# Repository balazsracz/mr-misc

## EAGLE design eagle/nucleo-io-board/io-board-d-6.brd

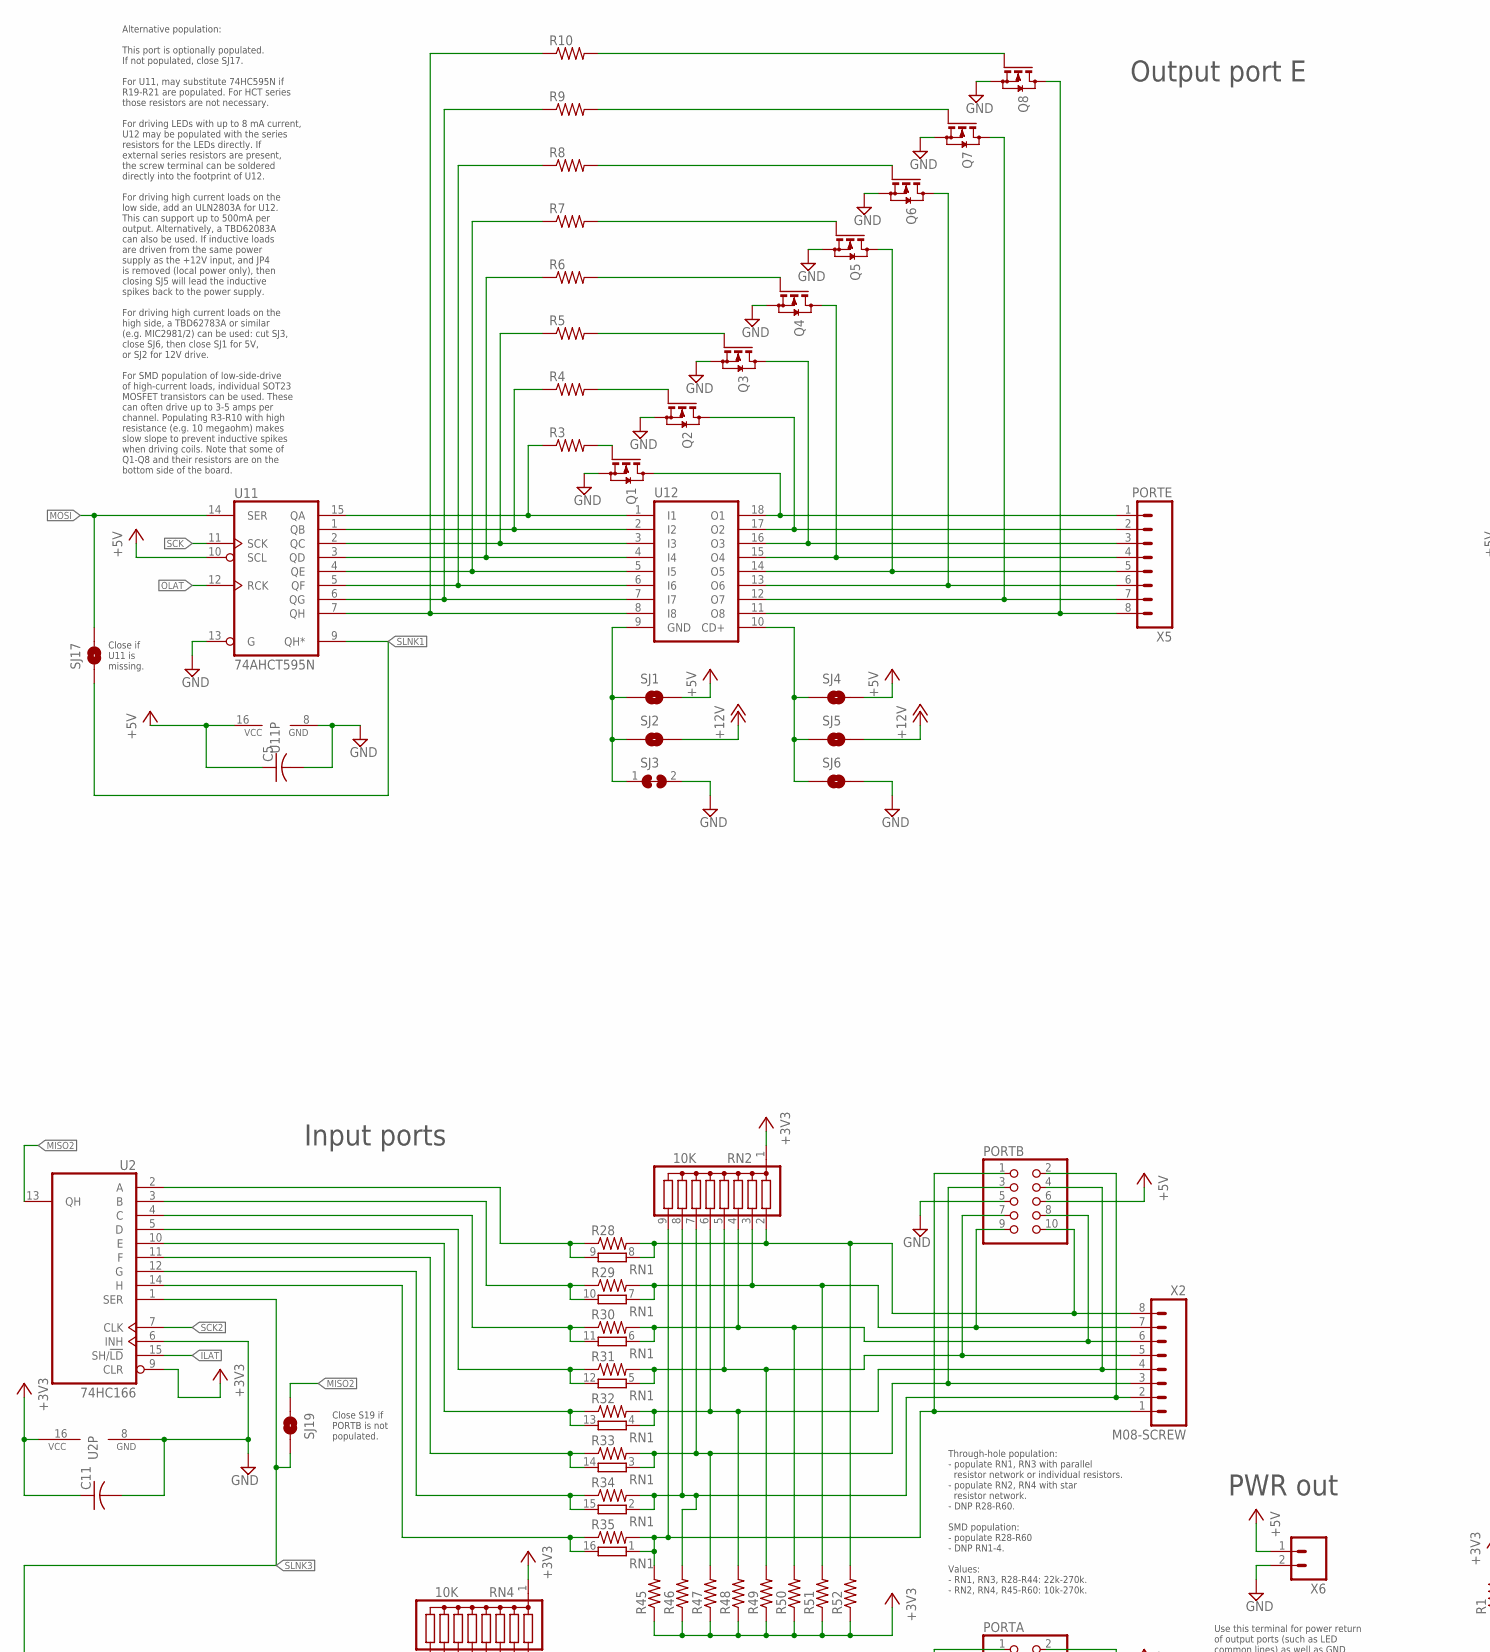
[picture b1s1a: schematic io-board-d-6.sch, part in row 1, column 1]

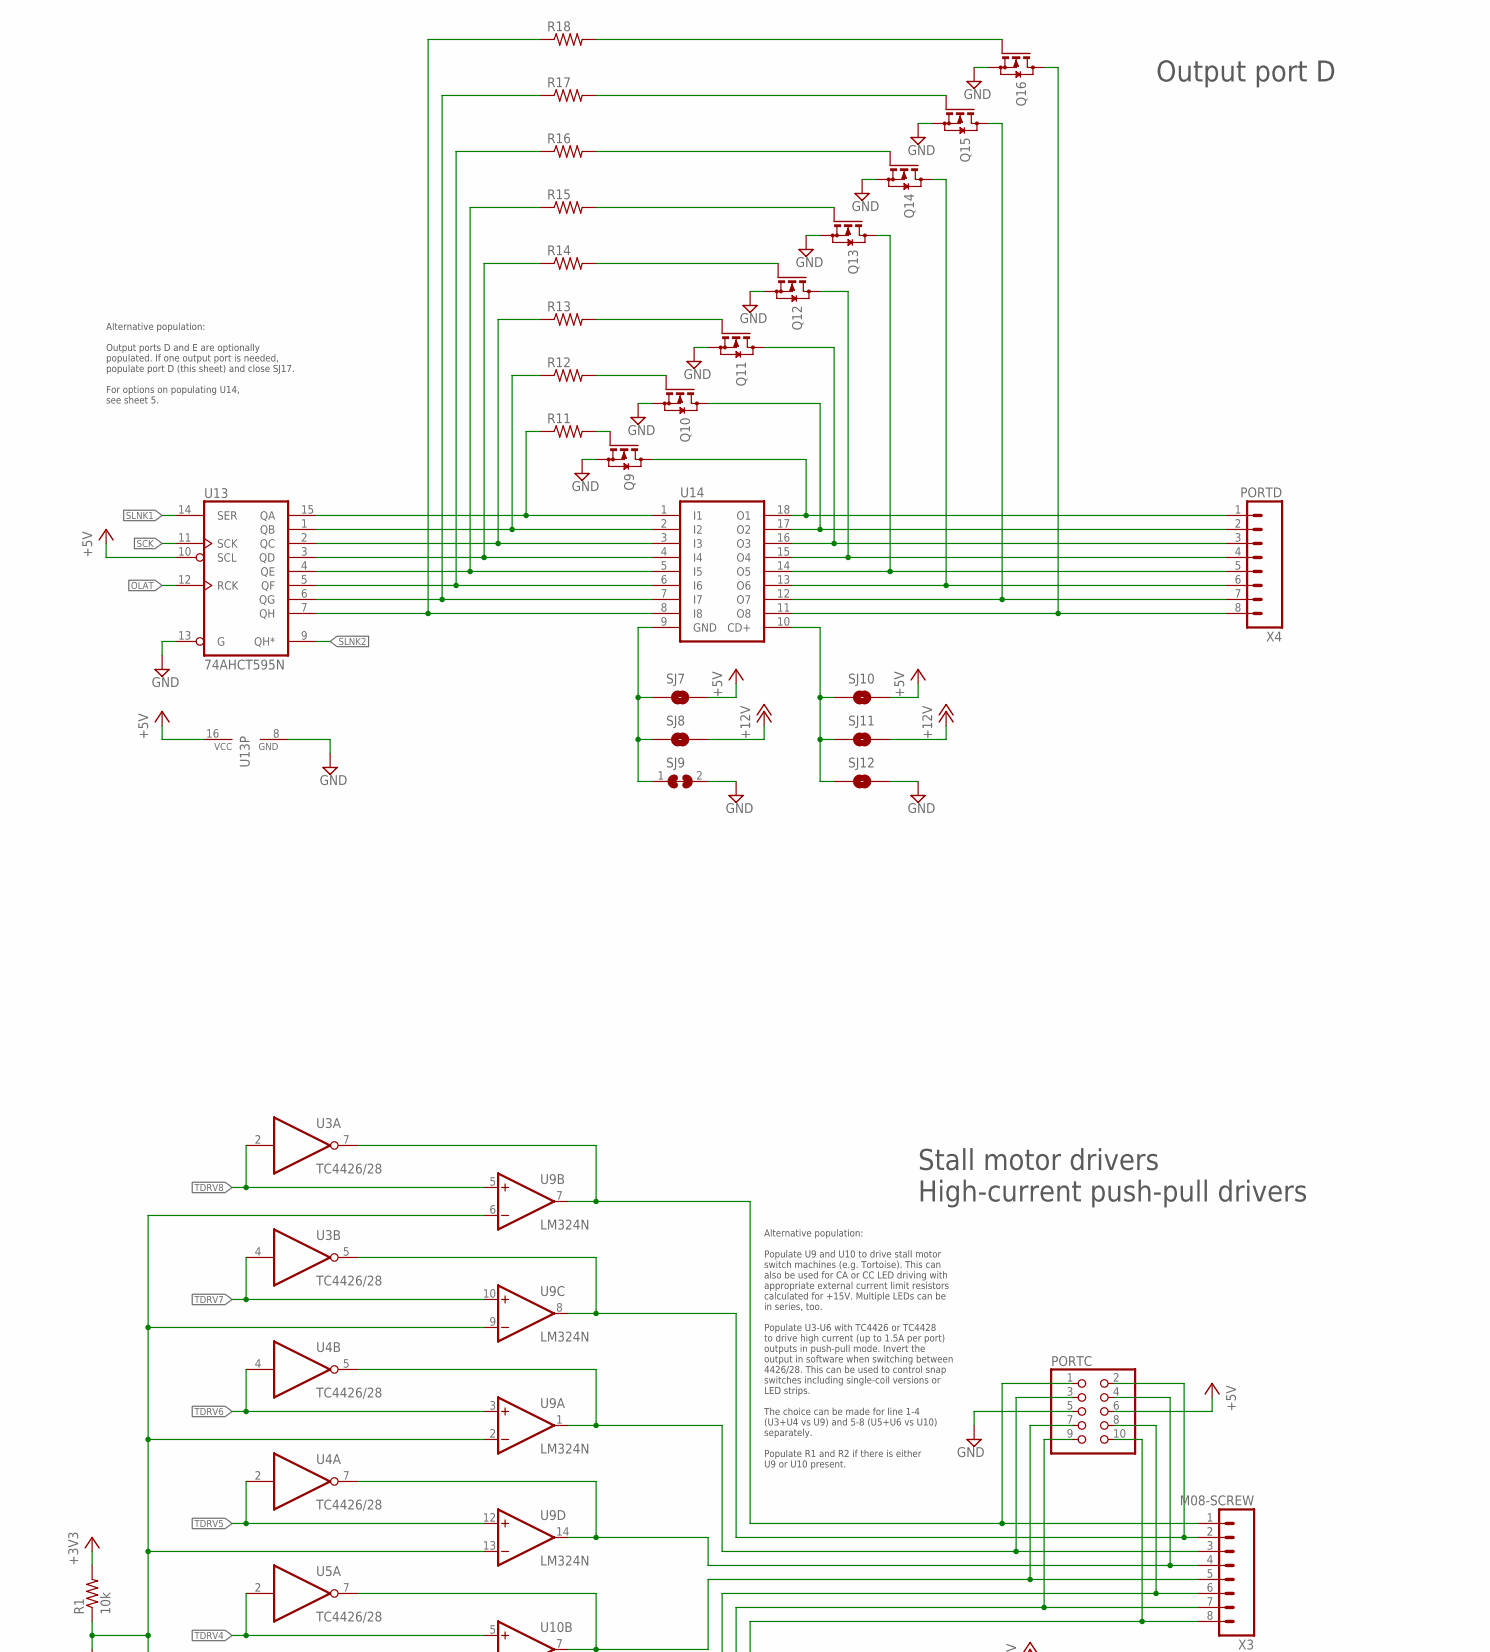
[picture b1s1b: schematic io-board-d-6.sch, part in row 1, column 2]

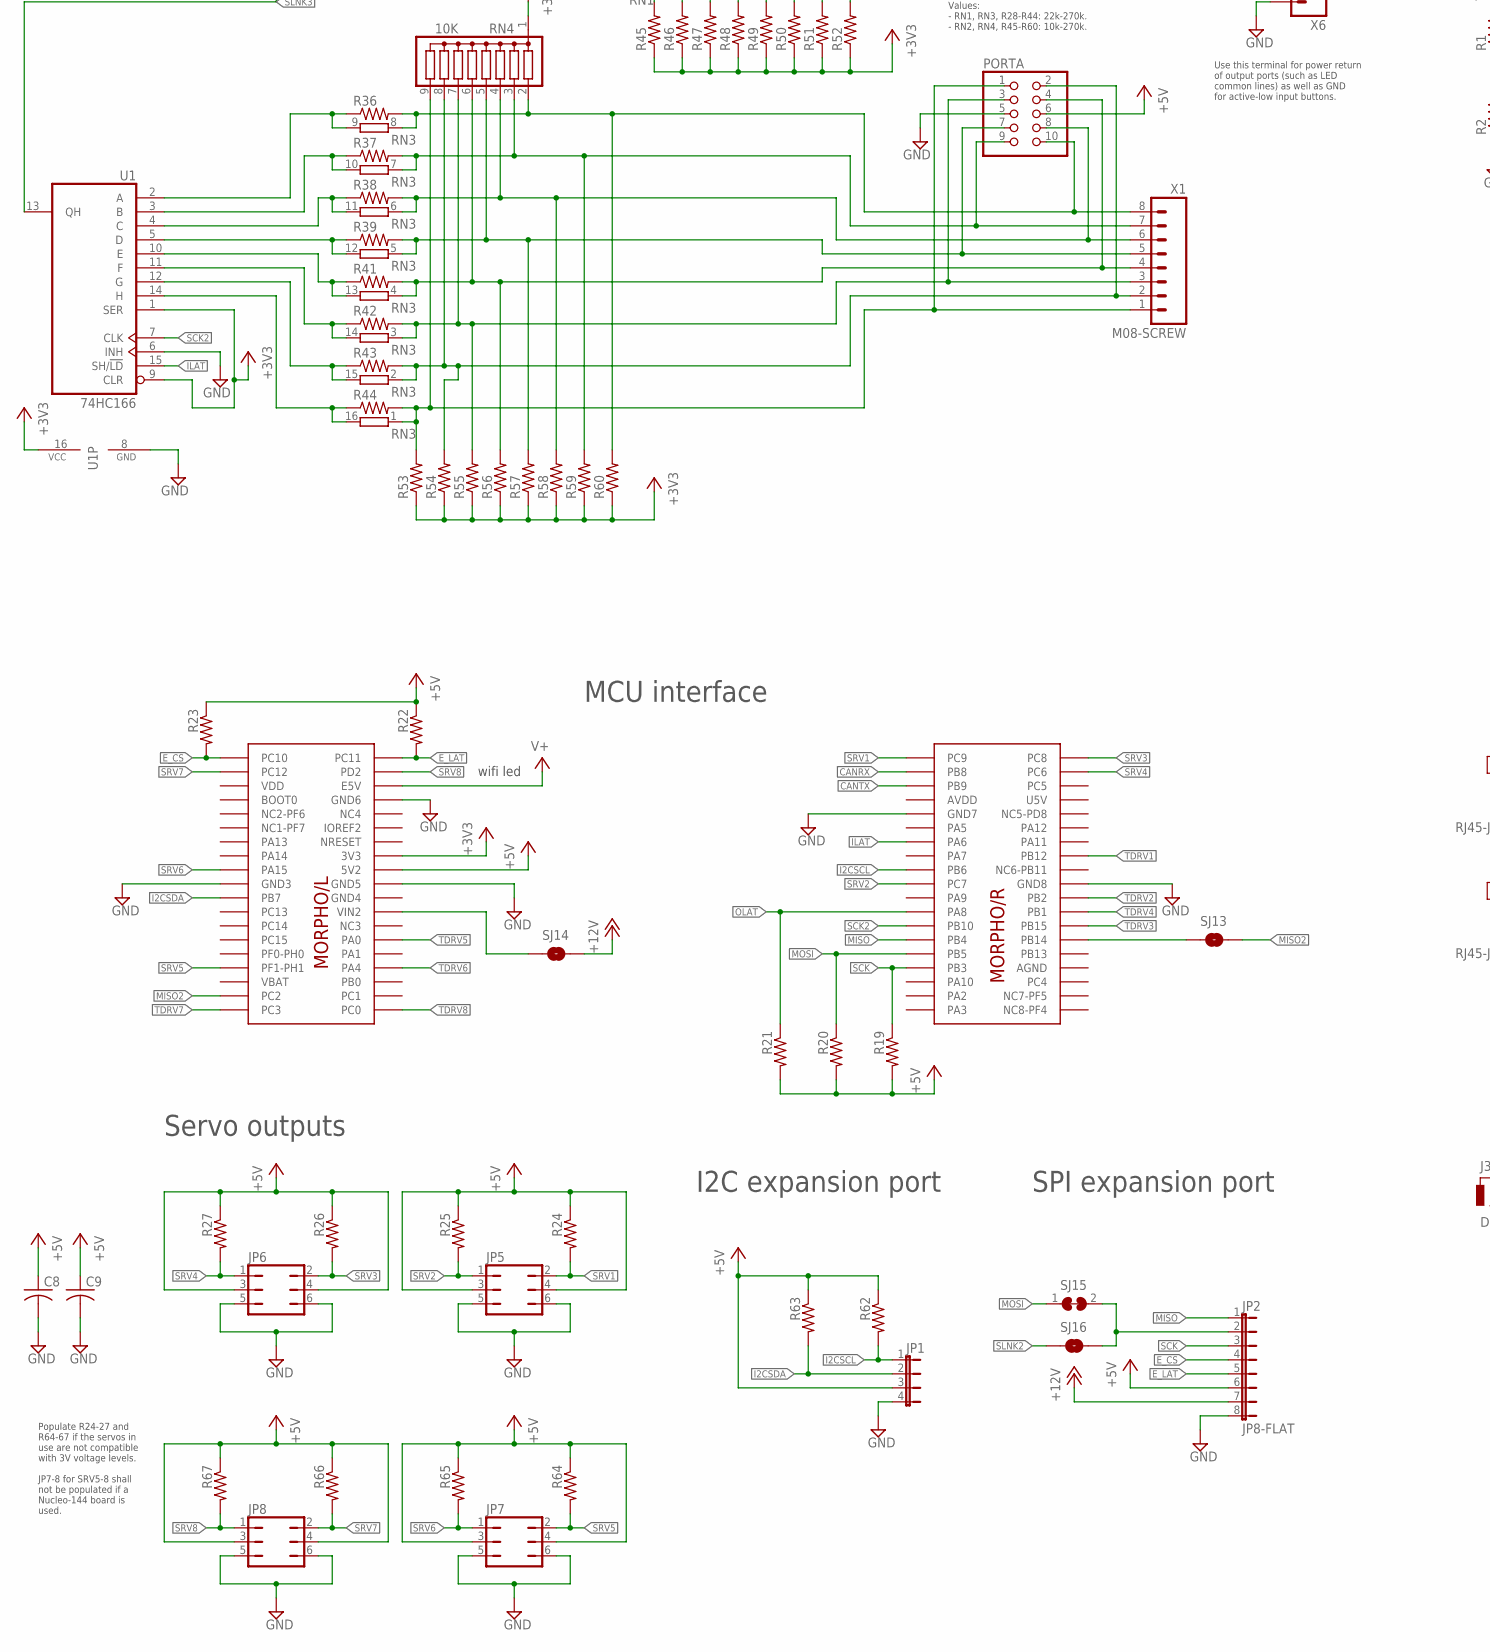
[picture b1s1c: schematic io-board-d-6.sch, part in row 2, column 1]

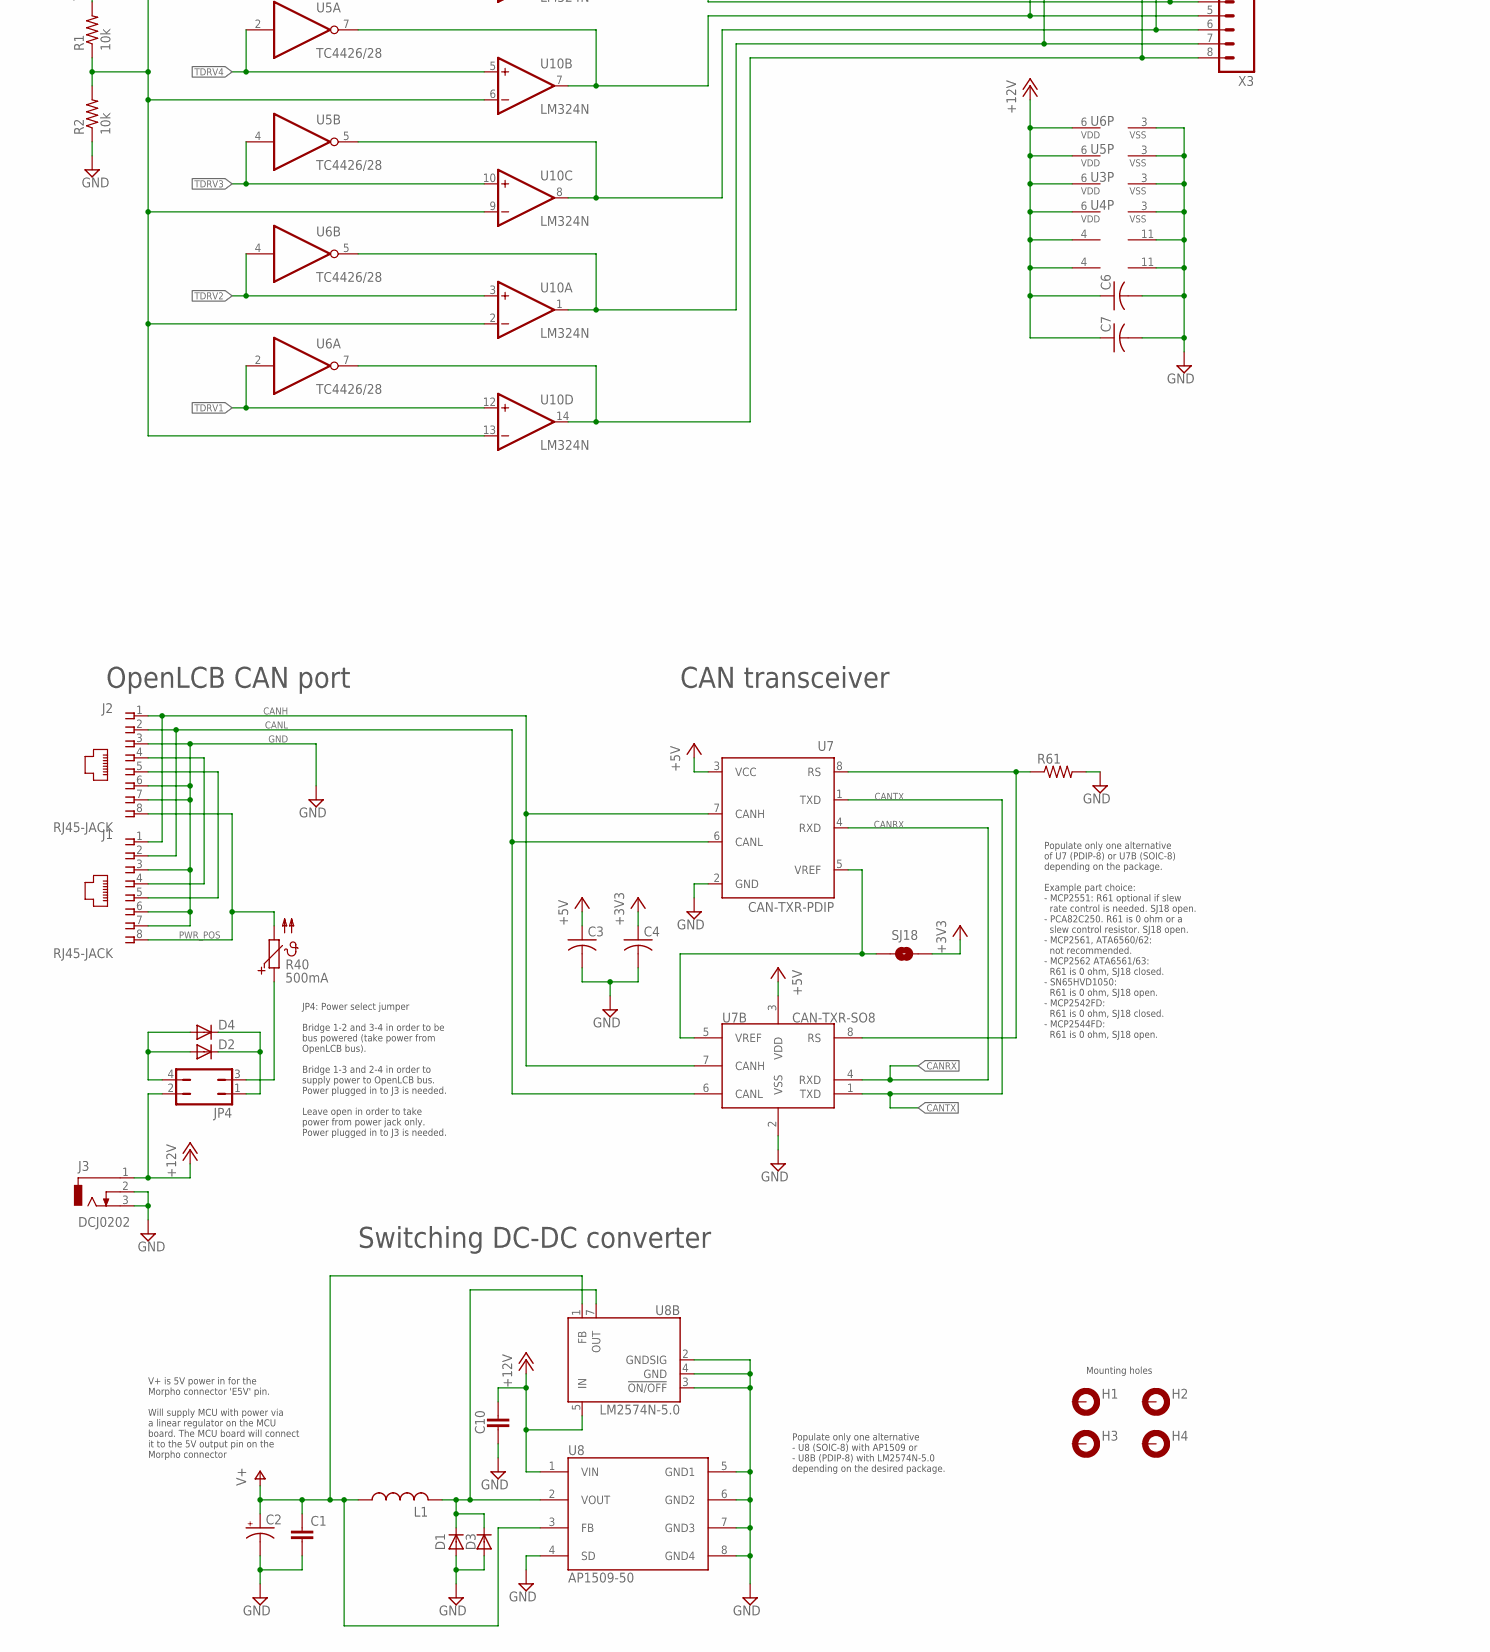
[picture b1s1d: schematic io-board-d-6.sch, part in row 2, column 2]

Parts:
+12V: 9-15V DC; POWER_USAGE
C1, C10: C-EUC1206; C1206
C2: CPOL-USE2.5-5; E2,5-5
C3, C4, C5, C11: C-USC0805; C0805
C6, C7, C8, C9: C-USC1206; C1206
D1, D2: DIODE-DO41-7.6; DO41-7.6
D3, D4: DIODEDO-214AA-NODOC; DO214AA-NODOC
H1, H2, H3, H4: MOUNT-PAD-ROUND3.3; 3,3-PAD
J1, J2: RJ45-JACK; RJ45-PULSE-E5J88
J3: DCJ0202
JP1: JP4-FLAT; JP4F
JP2: JP8-FLAT; JP8F
JP4: JP2Q
JP5, JP6, JP7, JP8: JP3Q
L1: L-US; L5-8,5
PORTA: PINHD-2X5CN; CON10M
PORTB: PINHD-2X5CN; CON10M
PORTC: PINHD-2X5CN; CON10M
Q1, Q2, Q3, Q4, Q5, Q6, Q7, Q8, Q9, Q10, Q11, Q12, Q13, Q14, Q15, Q16: BSS123; SOT23
R1, R2: 10k; R0805
R3, R4, R5, R6, R7, R8, R9, R10, R11, R12, R13, R14, R15, R16, R17, R18, R28, R29, R30, R31, R32, R33, R34, R35, R36, R37, R38, R39, R41, R42, R43, R44: R-US_R0603; R0603
R19, R20, R21, R22, R23, R24, R25, R26, R27, R61, R62, R63, R64, R65, R66, R67: R-US_R0805; R0805
R40: 500mA; PTC1812
R45, R46, R47, R48, R49, R50, R51, R52, R53, R54, R55, R56, R57, R58, R59, R60: R-US; R0603
RN1, RN3: 8R-P; DIL16
RN2, RN4: 10K; SIL9
SJ1, SJ2, SJ4, SJ5, SJ6, SJ7, SJ8, SJ10, SJ11, SJ12, SJ13, SJ14, SJ16, SJ17, SJ18, SJ19: SJRND2; SJ_RND2
SJ3, SJ9, SJ15: SJ-C; SJW-C
U1, U2: 74HC166; DIL16
U3, U4, U5, U6: TC4426/28; DIL08-LONG
U7: CAN-TXR-PDIP; DIL08
U7B: CAN-TXR-SO8; SO-08
U8: AP1509-50; SO-08
U8B: LM2574N-5.0; DIL08
U9, U10: LM324N; DIL14
U11, U13: 74AHCT595N; DIL16
U12, U14: ULN2803A; DIL18-THIN
U$1: NUCLEO_64_GENERIC; NUCLEO_BRD_BASE64
X1, X2, X3: M08-SCREW; 1X08_TERMINAL
X4: PORTD; 1X08_TERMINAL
X5: PORTE; 1X08_TERMINAL
X6: CONNECTOR-M023.5MM-LOCK; SCREWTERMINAL-3.5MM-2_LOCK

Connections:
+3V3: C4.1, C11.1, R1.2, R45.1, R46.1, R47.1, R48.1, R49.1, R50.1, R51.1, R52.1, R53.1, R54.1, R55.1, R56.1, R57.1, R58.1, R59.1, R60.1, RN2.1, RN4.1, SJ18.P$1 (1), U1.1 (SER), U1.9 (CLR), U1.16 (VCC), U2.9 (CLR), U2.16 (VCC), U$1.3V3
+5V: C3.1, C5.1, C8.1, C9.1, JP1.3, JP2.6, JP5.3, JP5.4, JP6.3, JP6.4, JP7.3, JP7.4, JP8.3, JP8.4, PORTA.6, PORTB.6, PORTC.6, R19.2, R20.2, R21.2, R22.1, R23.1, R24.1, R25.1, R26.1, R27.1, R62.1, R63.1, R64.1, R65.1, R66.1, R67.1, SJ1.P$2 (2), SJ4.P$2 (2), SJ7.P$2 (2), SJ10.P$2 (2), U7.3 (VCC), U7B.3 (VDD), U11.10 (SCL), U11.16 (VCC), U13.10 (SCL), U13.16 (VCC), U$1.5V2, X6.1
+12V: C6.1, C7.1, C10.1, J3.1, JP2.7, JP4.2, SJ2.P$2 (2), SJ5.P$2 (2), SJ8.P$2 (2), SJ11.P$2 (2), SJ14.P$2 (2), U3.6 (VDD), U4.6 (VDD), U5.6 (VDD), U6.6 (VDD), U8.1 (VIN), U8B.5 (IN), U9.4 (V+), U10.4 (V+)
AGND: U$1.AGND
AVDD: U$1.AVDD
CANH: J1.1, J2.1, U7.7 (CANH), U7B.7 (CANH)
CANL: J1.2, J2.2, U7.6 (CANL), U7B.6 (CANL)
CANRX: U7.4 (RXD), U7B.4 (RXD), U$1.PB8
CANTX: U7.1 (TXD), U7B.1 (TXD), U$1.PB9
CAN_RS: R61.1, U7.8 (RS), U7B.8 (RS)
CAN_VIO: SJ18.P$2 (2), U7.5 (VREF), U7B.5 (VREF)
CMPREF: R1.1, R2.2, U9.2 (-IN), U9.6 (-IN), U9.9 (-IN), U9.13 (-IN), U10.2 (-IN), U10.6 (-IN), U10.9 (-IN), U10.13 (-IN)
E_CS: JP2.4, R23.2, U$1.PC10
E_LAT: JP2.5, R22.2, U$1.PC11
E_MOSI: JP2.2, SJ15.2, SJ16.P$2 (2)
GND: C1.2, C2.-, C3.2, C4.2, C5.2, C6.2, C7.2, C8.2, C9.2, C10.2, C11.2, D1.A, D3.A, J1.3, J1.6, J1.7, J2.3, J2.6, J2.7, J3.2, J3.3, JP1.4, JP2.8, JP5.5, JP5.6, JP6.5, JP6.6, JP7.5, JP7.6, JP8.5, JP8.6, PORTA.5, PORTB.5, PORTC.5, Q1.2 (S), Q2.2 (S), Q3.2 (S), Q4.2 (S), Q5.2 (S), Q6.2 (S), Q7.2 (S), Q8.2 (S), Q9.2 (S), Q10.2 (S), Q11.2 (S), Q12.2 (S), Q13.2 (S), Q14.2 (S), Q15.2 (S), Q16.2 (S), R2.1, R61.2, SJ3.2, SJ6.P$2 (2), SJ9.2, SJ12.P$2 (2), U1.6 (INH), U1.8 (GND), U2.6 (INH), U2.8 (GND), U3.3 (VSS), U4.3 (VSS), U5.3 (VSS), U6.3 (VSS), U7.2 (GND), U7B.2 (VSS), U8.4 (SD), U8.5 (GND1), U8.6 (GND2), U8.7 (GND3), U8.8 (GND4), U8B.2 (GNDSIG), U8B.3 (!ON/OFF), U8B.4 (GND), U9.11 (V-), U10.11 (V-), U11.8 (GND), U11.13 (G), U13.8 (GND), U13.13 (G), U$1.GND3, U$1.GND5, U$1.GND6, U$1.GND7, U$1.GND8, X6.2
GND4: U$1.GND4
I2CSCL: JP1.1, R62.2, U$1.PB6
I2CSDA: JP1.2, R63.2, U$1.PB7
ILAT: U1.15 (SH/!LD), U2.15 (SH/!LD), U$1.PA6
LPOWA: SJ7.P$1 (1), SJ8.P$1 (1), SJ9.1, U14.9 (GND)
LPOWB: SJ10.P$1 (1), SJ11.P$1 (1), SJ12.P$1 (1), U14.10 (CD+)
MISO: JP2.1, U$1.PB4
MISO2: SJ13.P$2 (2), SJ19.P$2 (2), U2.13 (QH), U$1.PC2
MISO2_ALT: SJ13.P$1 (1), U$1.PB14
MOSI: R20.1, SJ15.1, SJ17.P$2 (2), U11.14 (SER), U$1.PB5
unnamed: R3.1, U11.15 (QA), U12.1 (I1)
unnamed: Q1.3 (D), U12.18 (O1), X5.1
unnamed: R4.1, U11.1 (QB), U12.2 (I2)
unnamed: J1.4, J2.4
unnamed: J1.5, J2.5
unnamed: PORTA.10, R36.2, R60.2, RN3.8 (1), RN4.2, X1.8
unnamed: Q2.3 (D), U12.17 (O2), X5.2
unnamed: R5.1, U11.2 (QC), U12.3 (I3)
unnamed: Q3.3 (D), U12.16 (O3), X5.3
unnamed: R6.1, U11.3 (QD), U12.4 (I4)
unnamed: Q4.3 (D), U12.15 (O4), X5.4
unnamed: R7.1, U11.4 (QE), U12.5 (I5)
unnamed: Q5.3 (D), U12.14 (O5), X5.5
unnamed: PORTA.9, R37.2, R59.2, RN3.7 (1), RN4.3, X1.7
unnamed: PORTA.8, R38.2, R58.2, RN3.6 (1), RN4.4, X1.6
unnamed: Q4.1 (G), R6.2
unnamed: R8.1, U11.5 (QF), U12.6 (I6)
unnamed: Q6.3 (D), U12.13 (O6), X5.6
unnamed: PORTA.4, R41.2, R56.2, RN3.4 (1), RN4.6, X1.4
unnamed: PORTA.3, R42.2, R55.2, RN3.3 (1), RN4.7, X1.3
unnamed: PORTB.8, R30.2, R50.2, RN1.6 (1), RN2.4, X2.6
unnamed: PORTA.1, R44.2, R53.2, RN3.1, RN4.9, X1.1
unnamed: R36.1, RN3.9 (2), U1.2 (A)
unnamed: R37.1, RN3.10 (2), U1.3 (B)
unnamed: PORTB.10, R28.2, R52.2, RN1.8 (1), RN2.2, X2.8
unnamed: PORTB.9, R29.2, R51.2, RN1.7 (1), RN2.3, X2.7
unnamed: Q5.1 (G), R7.2
unnamed: PORTB.7, R31.2, R49.2, RN1.5 (1), RN2.5, X2.5
unnamed: R38.1, RN3.11 (2), U1.4 (C)
unnamed: R39.1, RN3.12 (2), U1.5 (D)
unnamed: R41.1, RN3.13 (2), U1.10 (E)
unnamed: R42.1, RN3.14 (2), U1.11 (F)
unnamed: PORTB.4, R32.2, R48.2, RN1.4 (1), RN2.6, X2.4
unnamed: PORTB.3, R33.2, R47.2, RN1.3 (1), RN2.7, X2.3
unnamed: PORTB.2, R34.2, R46.2, RN1.2 (1), RN2.8, X2.2
unnamed: PORTB.1, R35.2, R45.2, RN1.1, RN2.9, X2.1
unnamed: R43.1, RN3.15 (2), U1.12 (G)
unnamed: R44.1, RN3.16 (2), U1.14 (H)
unnamed: R9.1, U11.6 (QG), U12.7 (I7)
unnamed: Q7.3 (D), U12.12 (O7), X5.7
unnamed: R10.1, U11.7 (QH), U12.8 (I8)
unnamed: Q8.3 (D), U12.11 (O8), X5.8
unnamed: Q6.1 (G), R8.2
unnamed: R28.1, RN1.9 (2), U2.2 (A)
unnamed: D2.C, D4.C, JP4.1
unnamed: D2.A, D4.A, JP4.4
unnamed: R29.1, RN1.10 (2), U2.3 (B)
unnamed: R30.1, RN1.11 (2), U2.4 (C)
unnamed: R31.1, RN1.12 (2), U2.5 (D)
unnamed: R32.1, RN1.13 (2), U2.10 (E)
unnamed: R33.1, RN1.14 (2), U2.11 (F)
unnamed: R34.1, RN1.15 (2), U2.12 (G)
unnamed: R35.1, RN1.16 (2), U2.14 (H)
unnamed: R11.1, U13.15 (QA), U14.1 (I1)
unnamed: JP4.3, R40.1
unnamed: SJ14.P$1 (1), U$1.VIN2
unnamed: Q7.1 (G), R9.2
unnamed: Q16.3 (D), U14.11 (O8), X4.8
unnamed: Q1.1 (G), R3.2
unnamed: Q2.1 (G), R4.2
unnamed: PORTA.7, R39.2, R57.2, RN3.5 (1), RN4.5, X1.5
unnamed: PORTA.2, R43.2, R54.2, RN3.2 (1), RN4.8, X1.2
unnamed: Q8.1 (G), R10.2
unnamed: Q9.3 (D), U14.18 (O1), X4.1
unnamed: Q3.1 (G), R5.2
unnamed: R12.1, U13.1 (QB), U14.2 (I2)
unnamed: Q10.3 (D), U14.17 (O2), X4.2
unnamed: R13.1, U13.2 (QC), U14.3 (I3)
unnamed: Q11.3 (D), U14.16 (O3), X4.3
unnamed: R14.1, U13.3 (QD), U14.4 (I4)
unnamed: Q12.3 (D), U14.15 (O4), X4.4
unnamed: R15.1, U13.4 (QE), U14.5 (I5)
unnamed: Q13.3 (D), U14.14 (O5), X4.5
unnamed: R16.1, U13.5 (QF), U14.6 (I6)
unnamed: Q14.3 (D), U14.13 (O6), X4.6
unnamed: R17.1, U13.6 (QG), U14.7 (I7)
unnamed: Q15.3 (D), U14.12 (O7), X4.7
unnamed: R18.1, U13.7 (QH), U14.8 (I8)
unnamed: Q9.1 (G), R11.2
unnamed: Q10.1 (G), R12.2
unnamed: Q11.1 (G), R13.2
unnamed: Q12.1 (G), R14.2
unnamed: Q13.1 (G), R15.2
unnamed: Q14.1 (G), R16.2
unnamed: Q15.1 (G), R17.2
unnamed: Q16.1 (G), R18.2
OLAT: R21.1, U11.12 (RCK), U13.12 (RCK), U$1.PA8
PWR_POS: J1.8, J2.8, R40.2
RPOWA: SJ1.P$1 (1), SJ2.P$1 (1), SJ3.1, U12.9 (GND)
RPOWB: SJ4.P$1 (1), SJ5.P$1 (1), SJ6.P$1 (1), U12.10 (CD+)
SCK: JP2.3, R19.1, U11.11 (SCK), U13.11 (SCK), U$1.PB3
SCK2: U1.7 (CLK), U2.7 (CLK), U$1.PB10
SLNK1: SJ17.P$1 (1), U11.9 (QH*), U13.14 (SER)
SLNK2: SJ16.P$1 (1), U13.9 (QH*)
SLNK3: SJ19.P$1 (1), U1.13 (QH), U2.1 (SER)
SRV1: JP5.2, R24.2, U$1.PC9
SRV2: JP5.1, R25.2, U$1.PC7
SRV3: JP6.2, R26.2, U$1.PC8
SRV4: JP6.1, R27.2, U$1.PC6
SRV5: JP7.2, R64.2, U$1.PF1-PH1
SRV6: JP7.1, R65.2, U$1.PA15
SRV7: JP8.2, R66.2, U$1.PC12
SRV8: JP8.1, R67.2, U$1.PD2
SW: D1.C, D3.C, L1.2, U8.2 (VOUT), U8B.7 (OUT)
TDRV1: U6.2 (I), U10.12 (+IN), U$1.PB12
TDRV2: U6.4 (I), U10.3 (+IN), U$1.PB2
TDRV3: U5.4 (I), U10.10 (+IN), U$1.PB15
TDRV4: U5.2 (I), U10.5 (+IN), U$1.PB1
TDRV5: U4.2 (I), U9.12 (+IN), U$1.PA0
TDRV6: U4.4 (I), U9.3 (+IN), U$1.PA4
TDRV7: U3.4 (I), U9.10 (+IN), U$1.PC3
TDRV8: U3.2 (I), U9.5 (+IN), U$1.PC0
TOUT1: PORTC.1, U3.7 (O), U9.7 (OUT), X3.1
TOUT2: PORTC.2, U3.5 (O), U9.8 (OUT), X3.2
TOUT3: PORTC.3, U4.5 (O), U9.1 (OUT), X3.3
TOUT4: PORTC.4, U4.7 (O), U9.14 (OUT), X3.4
TOUT5: PORTC.7, U5.7 (O), U10.7 (OUT), X3.5
TOUT6: PORTC.8, U5.5 (O), U10.8 (OUT), X3.6
TOUT7: PORTC.9, U6.5 (O), U10.1 (OUT), X3.7
TOUT8: PORTC.10, U6.7 (O), U10.14 (OUT), X3.8
U5V: U$1.U5V
V+: C1.1, C2.+, L1.1, U8.3 (FB), U8B.1 (FB), U$1.E5V
VBAT: U$1.VBAT
VDD: U$1.VDD

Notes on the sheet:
wifi led
Servo outputs
I2C expansion port
SPI expansion port
MCU interface
Populate only one alternative of U7 (PDIP-8) or U7B (SOIC-8) depending on the package. Example part choice: - MCP2551: R61 optional if slew rate control is needed. SJ18 open. - PCA82C250. R61 is 0 ohm or a slew control resistor. SJ18 open. - MCP2561, ATA6560/62: not recommended. - MCP2562 ATA6561/6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
OpenLCB CAN port
CAN transceiver
JP4: Power select jumper Bridge 1-2 and 3-4 in order to be bus powered (take power from OpenLCB bus). Bridge 1-3 and 2-4 in order to supply power to OpenLCB bus. Power plugged in to J3 is needed. Leave open in order to take power from power jack only. Power plugged in to J3 is needed.
Switching DC-DC converter
Populate only one alternative - U8 (SOIC-8) with AP1509 or - U8B (PDIP-8) with LM2574N-5.0 depending on the desired package.
V+ is 5V power in for the Morpho connector 'E5V' pin. Will supply MCU with power via a linear regulator on the MCU board. The MCU board will connect it to the 5V output pin on the Morpho connector
Mounting holes
Input ports
Through-hole population: - populate RN1, RN3 with parallel resistor network or individual resistors. - populate RN2, RN4 with star resistor network. - DNP R28-R60. SMD population: - populate R28-R60 - DNP RN1-4. Values: - RN1, RN3, R28-R44: 22k-270k. - RN2, RN4, R45-R60: 10k-270k.
Stall motor drivers High-current push-pull drivers
Alternative population: Populate U9 and U10 to drive stall motor switch machines (e.g. Tortoise). This can also be used for CA or CC LED driving with appropriate external current limit resistors calculated for +15V. Multiple LEDs can be in series, too. Populate U3-U6 with TC4426 or TC4428 to drive 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
Close if U11 is missing.
Alternative population: This port is optionally populated. If not populated, close SJ17. For U11, may substitute 74HC595N if R19-R21 are populated. For HCT series those resistors are not necessary. For driving LEDs with up to 8 mA current, U12 may be populated with the series resistors for the LEDs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
Alternative population: Output ports D and E are optionally populated. If one output port is needed, populate port D (this sheet) and close SJ17. For options on populating U14, see sheet 5.
Output port E
Output port D
PWR out
Use this terminal for power return of output ports (such as LED common lines) as well as GND for active-low input buttons.
Populate R24-27 and R64-67 if the servos in use are not compatible with 3V voltage levels. JP7-8 for SRV5-8 shall not be populated if a Nucleo-144 board is used.
Close S19 if PORTB is not populated.

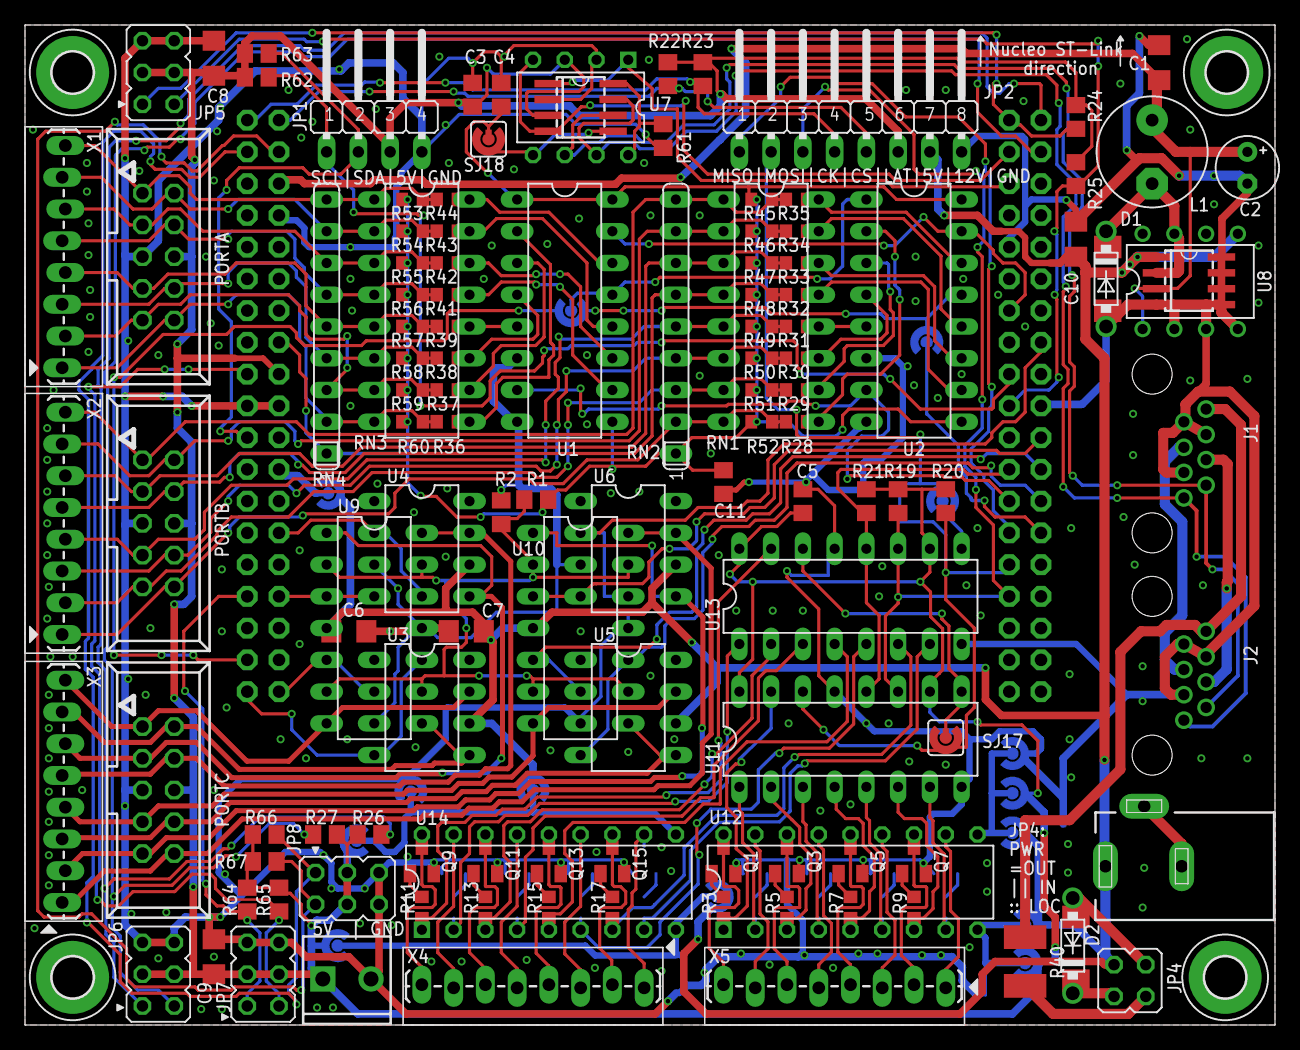
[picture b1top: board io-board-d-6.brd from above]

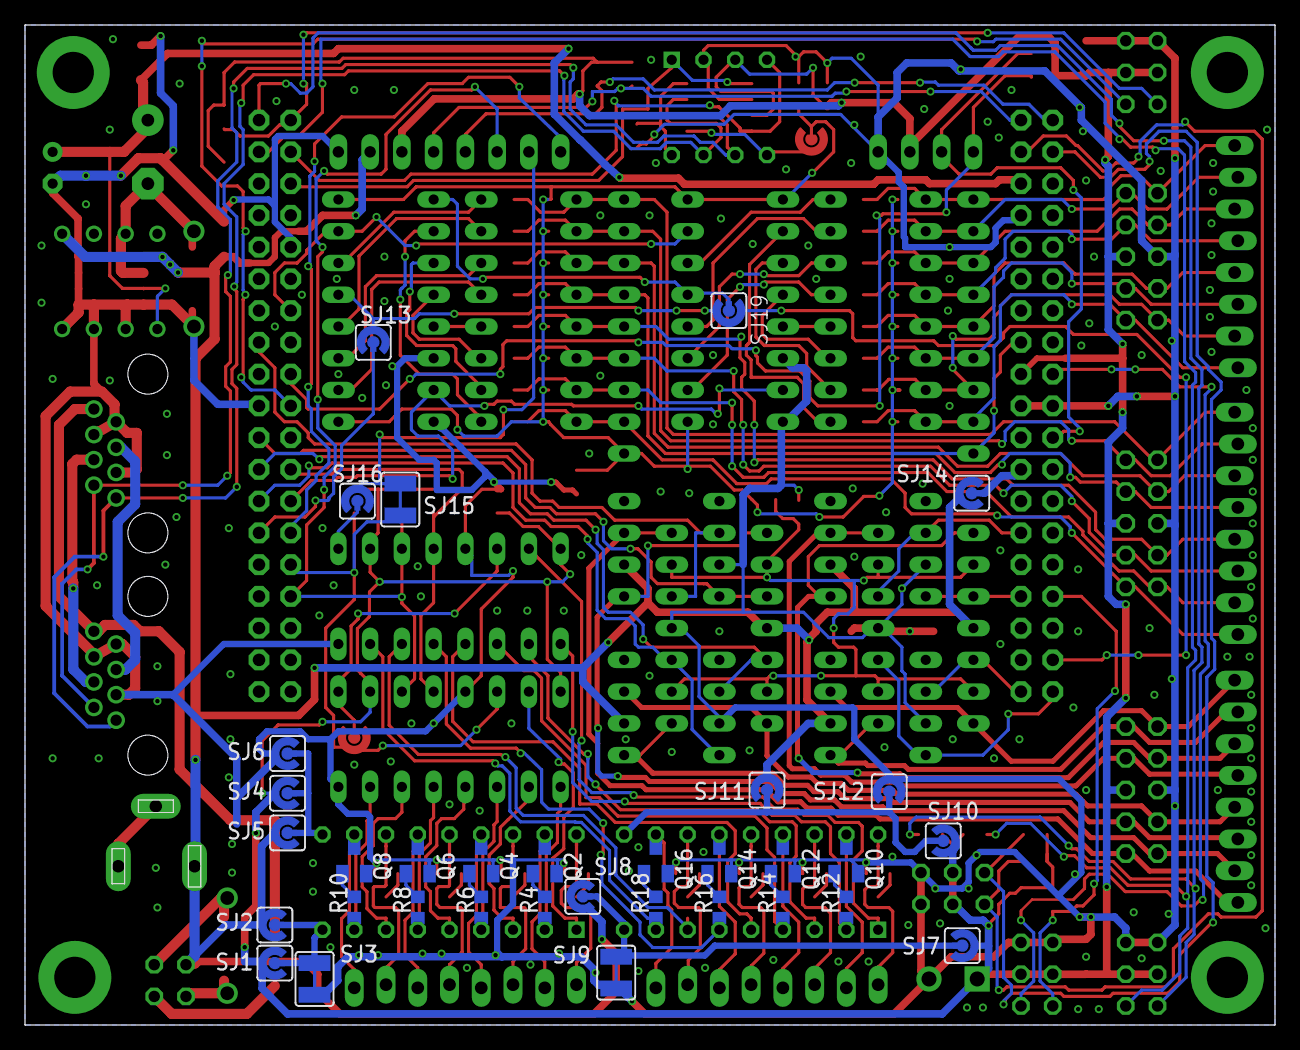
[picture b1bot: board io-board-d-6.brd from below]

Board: 2 copper layers, 100.0 x 80.0 mm, 163 parts (33 on the bottom side), 144 nets.

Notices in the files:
eagle/nucleo-io-board/io-board-d-6.sch:
LICENSE: [placeholder for license]
